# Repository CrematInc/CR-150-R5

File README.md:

# CR-150-R5
KiCad files for Cremat's CR-150-R5, an evaluation board for Cremat's charge sensitive preamplifier modules CR-11X. 
Includes a provision for wall mounted power supply.

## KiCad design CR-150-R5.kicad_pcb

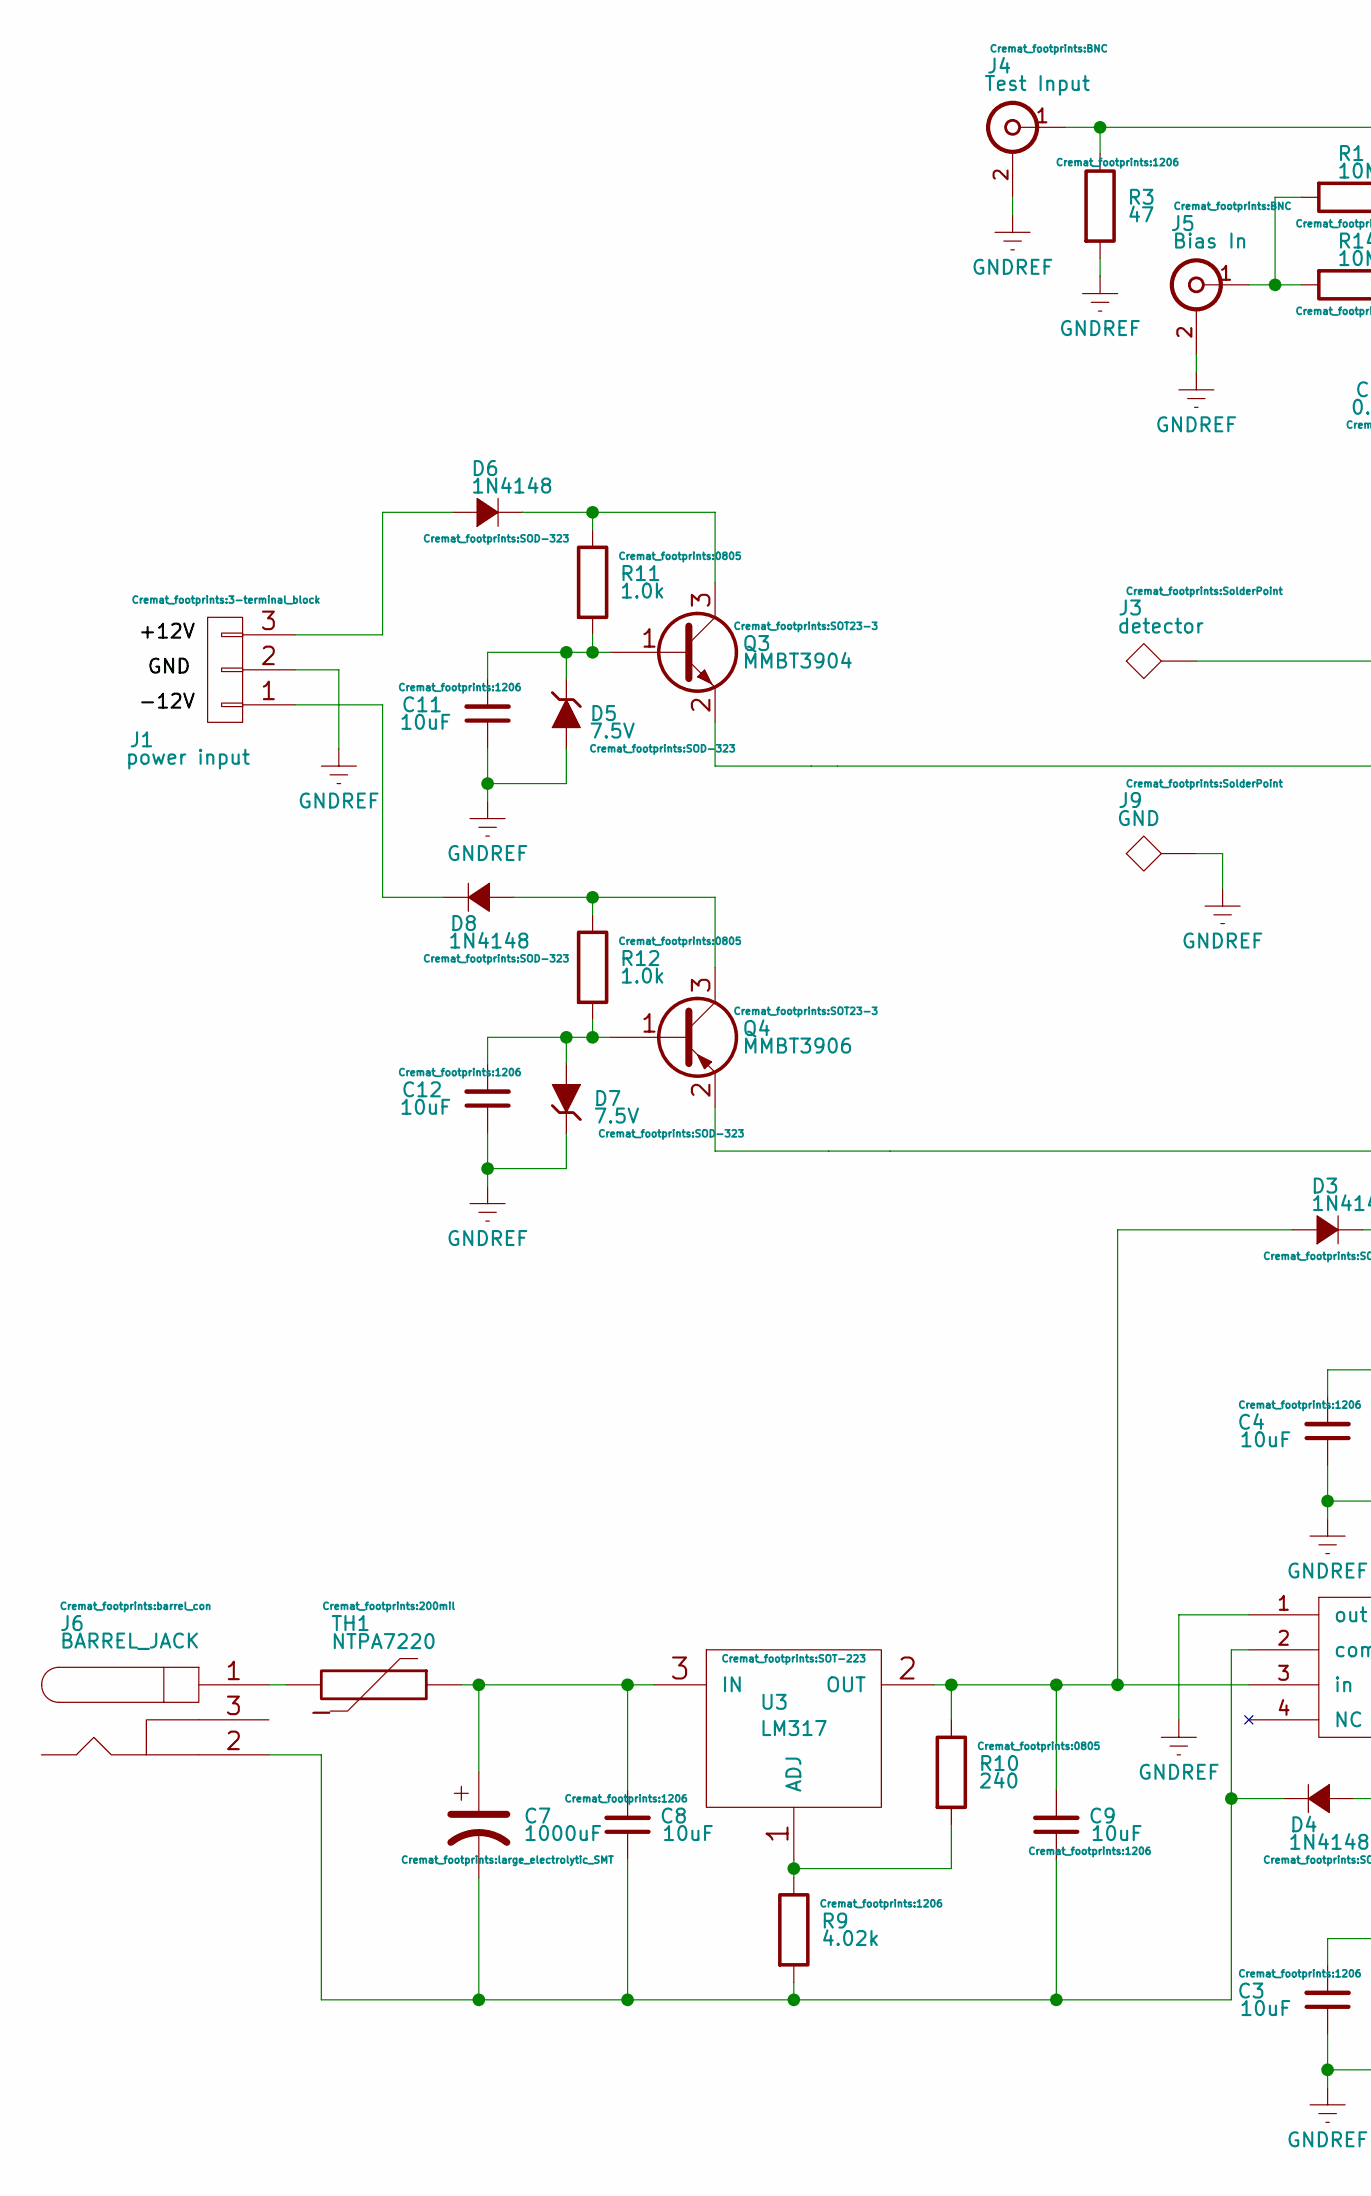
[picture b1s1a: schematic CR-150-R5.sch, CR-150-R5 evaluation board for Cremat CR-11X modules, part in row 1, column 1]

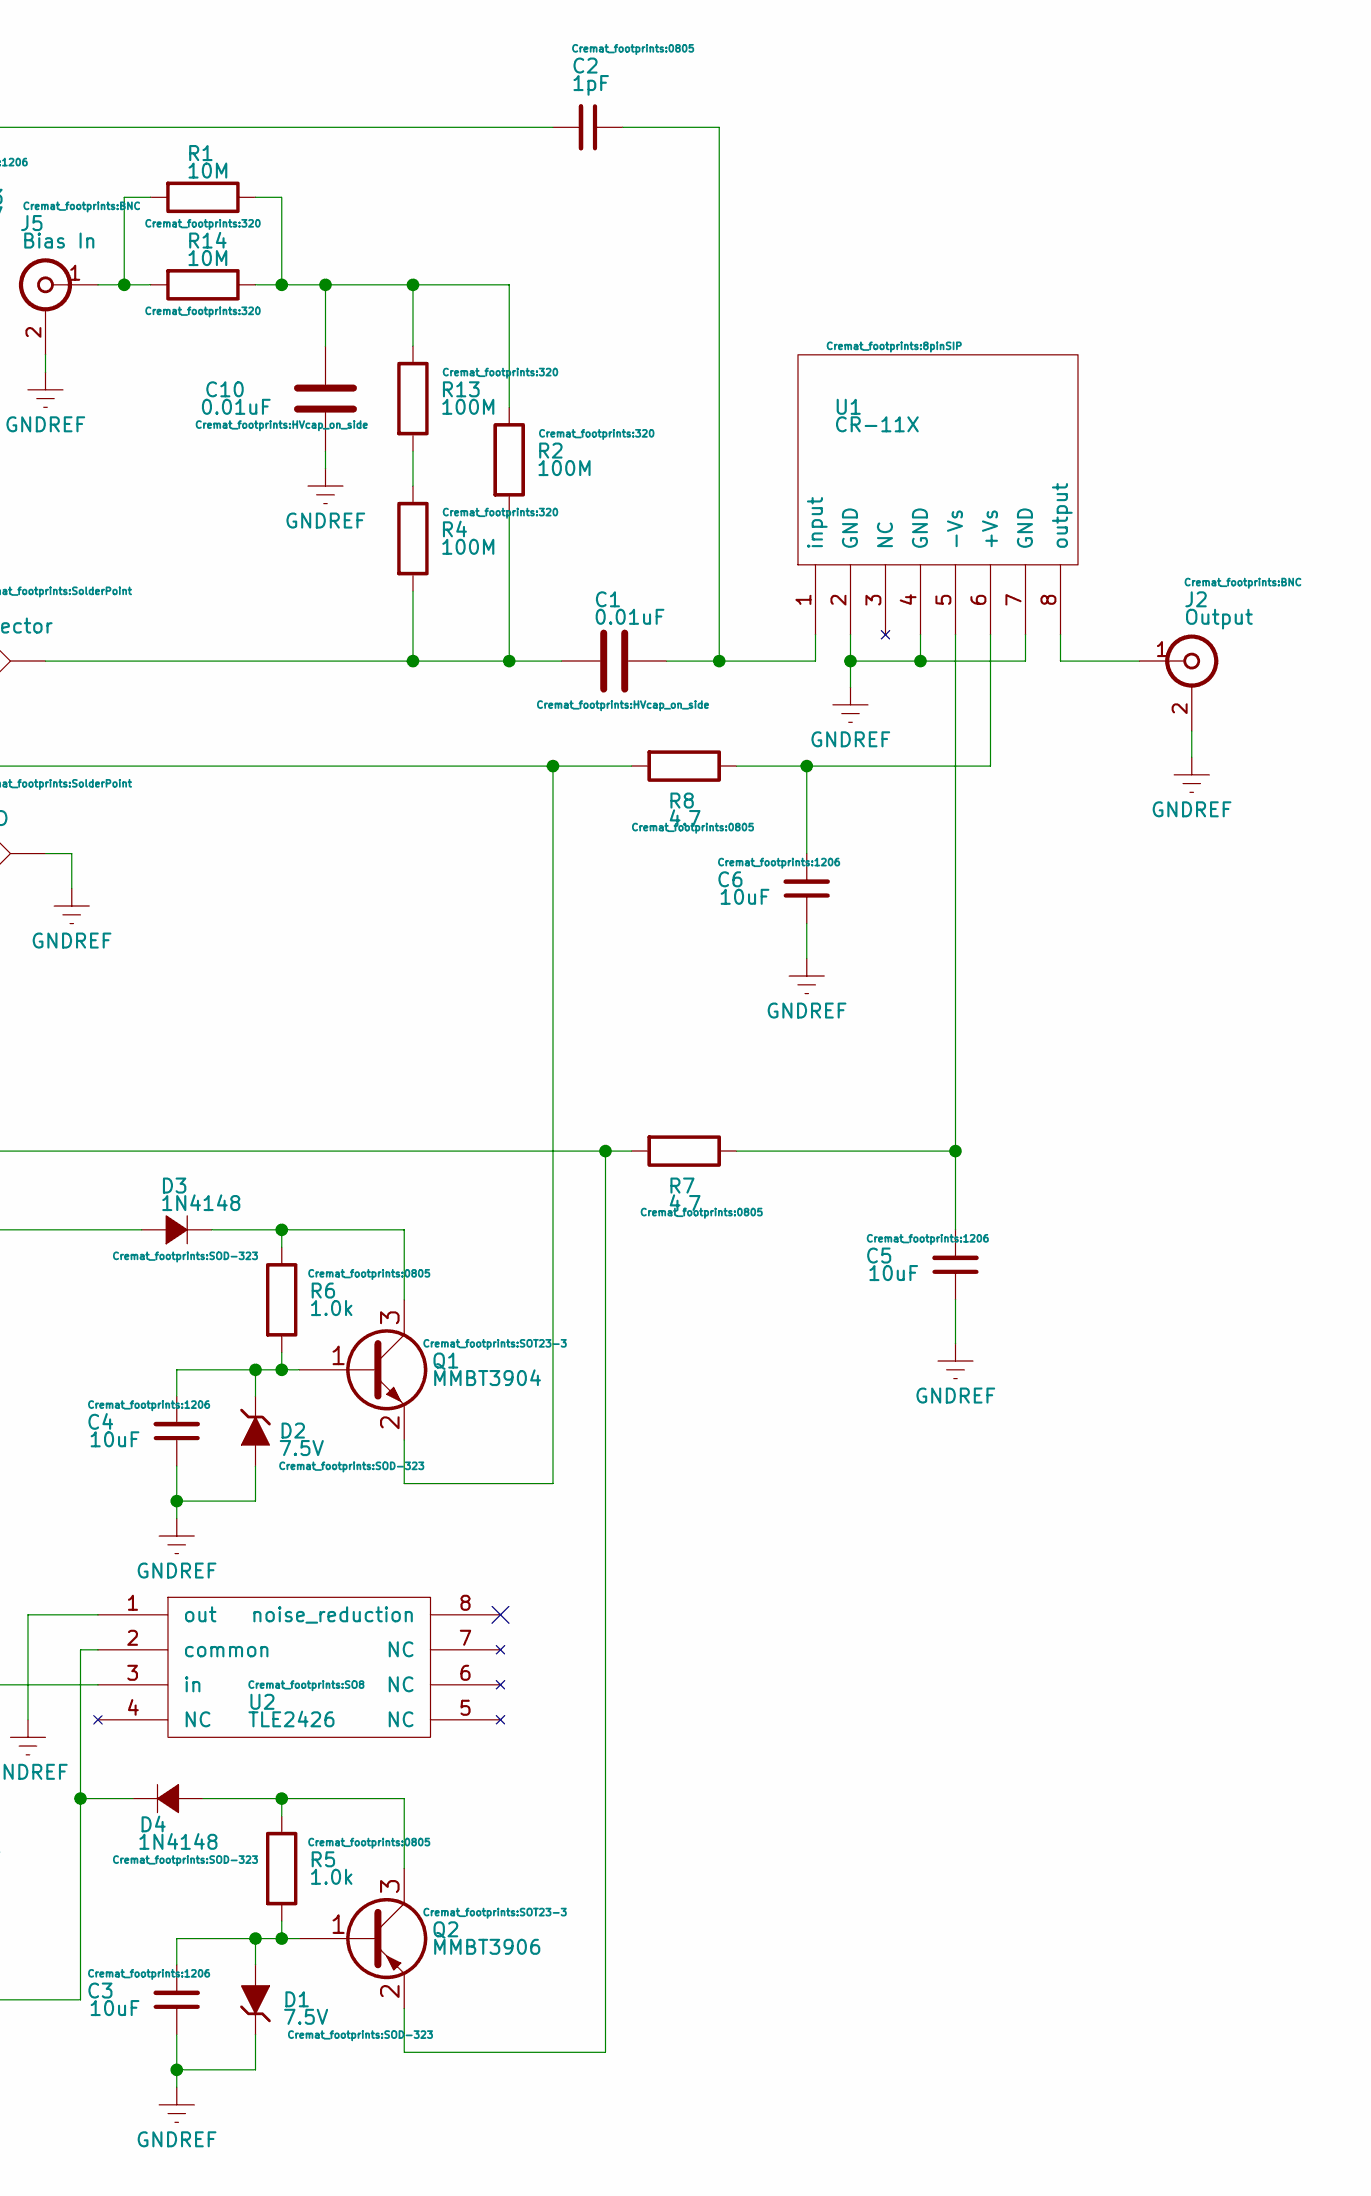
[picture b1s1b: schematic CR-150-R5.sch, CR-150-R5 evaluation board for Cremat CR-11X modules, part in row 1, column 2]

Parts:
C1, C10: 0.01uF; HVcap_on_side
C2: 1pF; 0805
C3, C4, C5, C6, C8, C9, C11, C12: 10uF; 1206
C7: 1000uF; large_electrolytic_SMT
D1, D2, D5, D7: 7.5V; SOD-323
D3, D4, D6, D8: 1N4148; SOD-323
J1: power input; 3-terminal_block
J2: Output; BNC
J3: detector; SolderPoint
J4: Test Input; BNC
J5: Bias In; BNC
J6: BARREL_JACK; barrel_con
J9: GND; SolderPoint
Q1, Q3: MMBT3904; SOT23-3
Q2, Q4: MMBT3906; SOT23-3
R1, R14: 10M; 320
R2, R4, R13: 100M; 320
R3: 47; 1206
R5, R6, R11, R12: 1.0k; 0805
R7, R8: 4.7; 0805
R9: 4.02k; 1206
R10: 240; 0805
TH1: NTPA7220; 200mil
U1: CR-11X; 8pinSIP
U2: TLE2426; SO8
U3: LM317; SOT-223

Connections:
GNDREF: C3.1, C4.1, C5.1, C6.1, C10.1, C11.1, C12.1, D1.2 (K), D2.1 (A), D5.1 (A), D7.2 (K), J1.2, J2.2 (Ext), J4.2 (Ext), J5.2 (Ext), J9.1, R3.2, U1.2 (GND), U1.4 (GND), U1.7 (GND), U2.1 (out)
unnamed: C1.1, J3.1, R2.2, R4.2
unnamed: C1.2, C2.1, U1.1 (input)
unnamed: C2.2, J4.1 (In), R3.1
unnamed: C3.2, D1.1 (A), Q2.1 (B), R5.2
unnamed: C4.2, D2.2 (K), Q1.1 (B), R6.2
unnamed: C5.2, R7.1, U1.5 (-Vs)
unnamed: C6.2, R8.1, U1.6 (+Vs)
unnamed: C7.1, C8.2, TH1.1, U3.3 (IN)
unnamed: C7.2, C8.1, C9.1, D4.2 (C), J6.2, R9.2, U2.2 (common)
unnamed: C9.2, D3.1 (A), R10.1, U2.3 (in), U3.2 (OUT)
unnamed: C10.2, R1.1, R2.1, R13.1, R14.1
unnamed: C11.2, D5.2 (K), Q3.1 (B), R11.2
unnamed: C12.2, D7.1 (A), Q4.1 (B), R12.2
unnamed: D3.2 (C), Q1.3 (C), R6.1
unnamed: D4.1 (A), Q2.3 (C), R5.1
unnamed: D6.1 (A), J1.3
unnamed: D6.2 (C), Q3.3 (C), R11.1
unnamed: D8.1 (A), Q4.3 (C), R12.1
unnamed: D8.2 (C), J1.1
unnamed: J2.1 (In), U1.8 (output)
unnamed: J5.1 (In), R1.2, R14.2
unnamed: J6.1, TH1.2
unnamed: Q1.2 (E), Q3.2 (E), R8.2
unnamed: Q2.2 (E), Q4.2 (E), R7.2
unnamed: R9.1, R10.2, U3.1 (ADJ)
unnamed: R4.1, R13.2

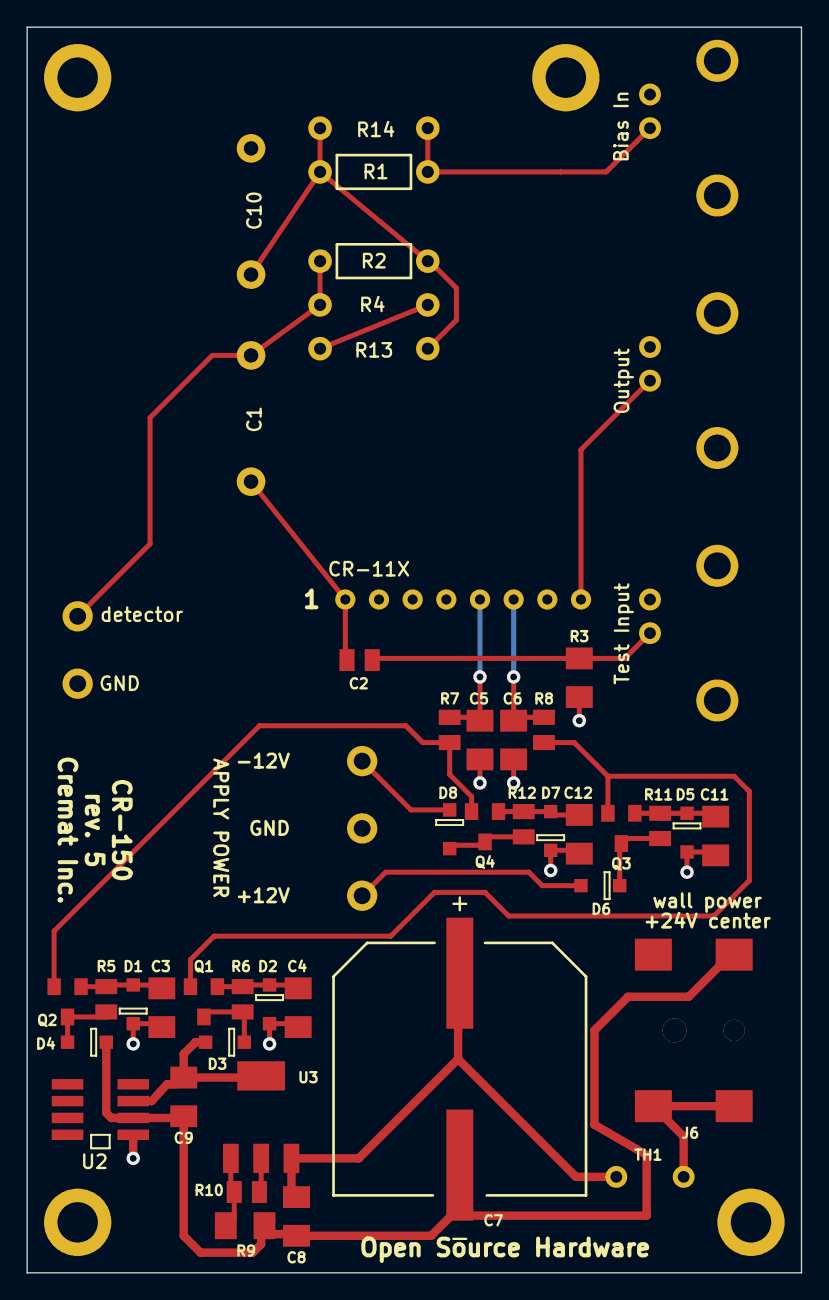
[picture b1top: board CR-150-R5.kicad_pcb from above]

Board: 2 copper layers, 58.4 x 94.0 mm, 49 parts (0 on the bottom side), 27 nets.

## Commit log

2015-11-24 :tada: Added .gitattributes & .gitignore files
2015-11-24 evaluation board for Cremat's charge sensitive preamplifier modules CR-11X
    KiCad files for Cremat's CR-150-R5, an evaluation board for Cremat's
    charge sensitive preamplifier modules CR-11X Includes Schematic, layout,
    and Gerber files. Also a BOM.

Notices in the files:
CR-150-R5.sch:
This is Open Source Hardware under the MIT license. http://opensource.org/licenses/MIT
